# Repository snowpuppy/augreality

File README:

Aug Reality Cornell Cup Project ==
==================================

INTRODUCTION =
==============
This project aims to build an augmented reality simulator device
using a headset and the Intel DE2-i150 development board for the Cornell Cup
Competition. The headset is a custom design which has 3d graphics,
head tracking, gps positioning, and a wide field of view.
This is phase2 of the project. Documentation for phase1 and phase2 can be found
in our doc/ folder. The headset src/ folder is subdivided into all of the software
modules for this project.

DIRECTORY STRUCTURE =
=====================

## headset
##########

$$ headset/src
    This directory contains all source code for the Headset.

$$ headset/test
    This directory contains all test code for the headset (usually proof of concept or simulation code.)

$$ headset/doc
    This directory contains specific documentation related to the headset.

## doc
######
  This directory contains all general documenation for the top level design.

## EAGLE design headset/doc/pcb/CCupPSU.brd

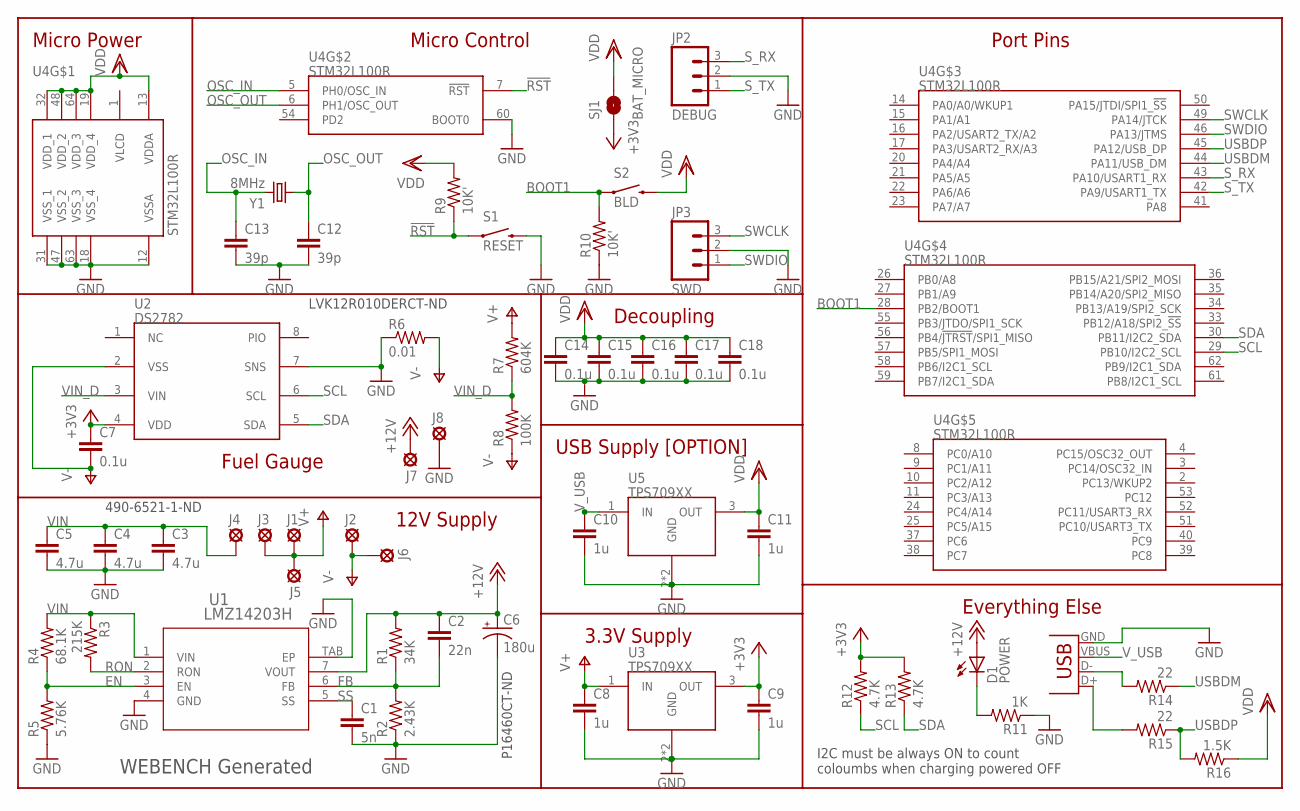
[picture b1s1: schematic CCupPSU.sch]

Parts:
C1: 5n; 1206
C2: 22n; 1206
C3, C4, C5: 4.7u; 1206
C6: 180u; PANASONIC_E
C7, C14, C15, C16, C17, C18: 0.1u; 1206
C8, C9, C10, C11: 1u; 1206
C12, C13: 39p; 1206
D1: POWER; LED-1206
J1, J2, J3, J4, J5, J6, J7, J8: SE14
JP1: USBSMD; USB-MINIB
JP2: DEBUG; 1X03
JP3: SWD; 1X03
R1: 34K; 1206
R2: 2.43K; 1206
R3: 215K; 1206
R4: 68.1K; 1206
R5: 5.76K; 1206
R6: 0.01; 1206
R7: 604K; 1206
R8: 100K; 1206
R9, R10: 10K'; 1206
R11: 1K; 1206
R12, R13: 4.7K; 1206
R14, R15: 22; 1206
R16: 1.5K; 1206
S1: RESET; TACTILE-PTH
S2: BLD; TACTILE-PTH
SJ1: BAT_MICRO; SJ_2S-TRACE
U1: LMZ14203H; TZA07A
U2: DS2782; TSSOP8
U3, U5: TPS709XX; SOT223
U4: STM32L100R; TQFP64
Y1: 8MHz; HC49US

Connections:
!RST!: R9.1, S1.1, U4.7 (!RST!)
+3V3: C7.1, C9.1, R12.2, R13.2, SJ1.1, U2.4 (VDD), U3.3 (OUT)
+12V: C2.1, C6.+, D1.A, J7.MP, R1.2, U1.7 (VOUT)
BOOT1: R10.2, S2.1, U4.28 (PB2/BOOT1)
EN: R4.1, R5.2, U1.3 (EN)
FB: C2.2, R1.1, R2.2, U1.6 (FB)
GND: C1.2, C3.2, C4.2, C5.2, C6.-, C8.2, C9.2, C10.2, C11.2, C12.2, C13.2, C14.2, C15.2, C16.2, C17.2, C18.2, J8.MP, JP1.GND, JP2.2, JP3.2, R2.1, R5.1, R6.1, R10.1, R11.1, S1.3 (2), U1.4 (GND), U1.TAB (EP), U2.7 (SNS), U3.2 (GND), U3.4 (GND), U4.12 (VSSA), U4.18 (VSS_4), U4.31 (VSS_1), U4.47 (VSS_2), U4.60 (BOOT0), U4.63 (VSS_3), U5.2 (GND), U5.4 (GND)
OSC_IN: C13.1, U4.5 (PH0/OSC_IN), Y1.2
OSC_OUT: C12.1, U4.6 (PH1/OSC_OUT), Y1.1
PLED: D1.C, R11.2
RON: R3.2, U1.2 (RON)
SCL: R12.1, U2.6 (SCL), U4.29 (PB10/I2C2_SCL)
SDA: R13.1, U2.5 (SDA), U4.30 (PB11/I2C2_SDA)
SS: C1.1, U1.5 (SS)
SWCLK: JP3.3, U4.49 (PA14/JTCK)
SWDIO: JP3.1, U4.46 (PA13/JTMS)
S_RX: JP2.3, U4.43 (PA10/USART1_RX)
S_TX: JP2.1, U4.42 (PA9/USART1_TX)
USBDM: R14.1, U4.44 (PA11/USB_DM)
USBDP: R15.1, R16.2, U4.45 (PA12/USB_DP)
USB_D+: JP1.D+, R15.2
USB_D-: JP1.D-, R14.2
V+: C8.1, J1.MP, J3.MP, J5.MP, R7.2, U3.1 (IN)
V-: C7.2, J2.MP, J6.MP, R6.2, R8.1, U2.2 (VSS)
VDD: C11.1, C14.1, C15.1, C16.1, C17.1, C18.1, R9.2, R16.1, S2.3 (2), SJ1.2, U4.13 (VDDA), U4.19 (VDD_4), U4.32 (VDD_1), U4.48 (VDD_2), U4.64 (VDD_3), U5.3 (OUT)
VIN: C3.1, C4.1, C5.1, J4.MP, R3.1, R4.2, U1.1 (VIN)
VIN_D: R7.1, R8.2, U2.3 (VIN)
V_USB: C10.1, JP1.VBUS, U5.1 (IN)

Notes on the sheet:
490-6521-1-ND
P16460CT-ND
12V Supply
WEBENCH Generated
LVK12R010DERCT-ND
3.3V Supply
Fuel Gauge
USB Supply [OPTION]
Micro Power
Micro Control
Decoupling
Port Pins
I2C must be always ON to count coloumbs when charging powered OFF
Everything Else

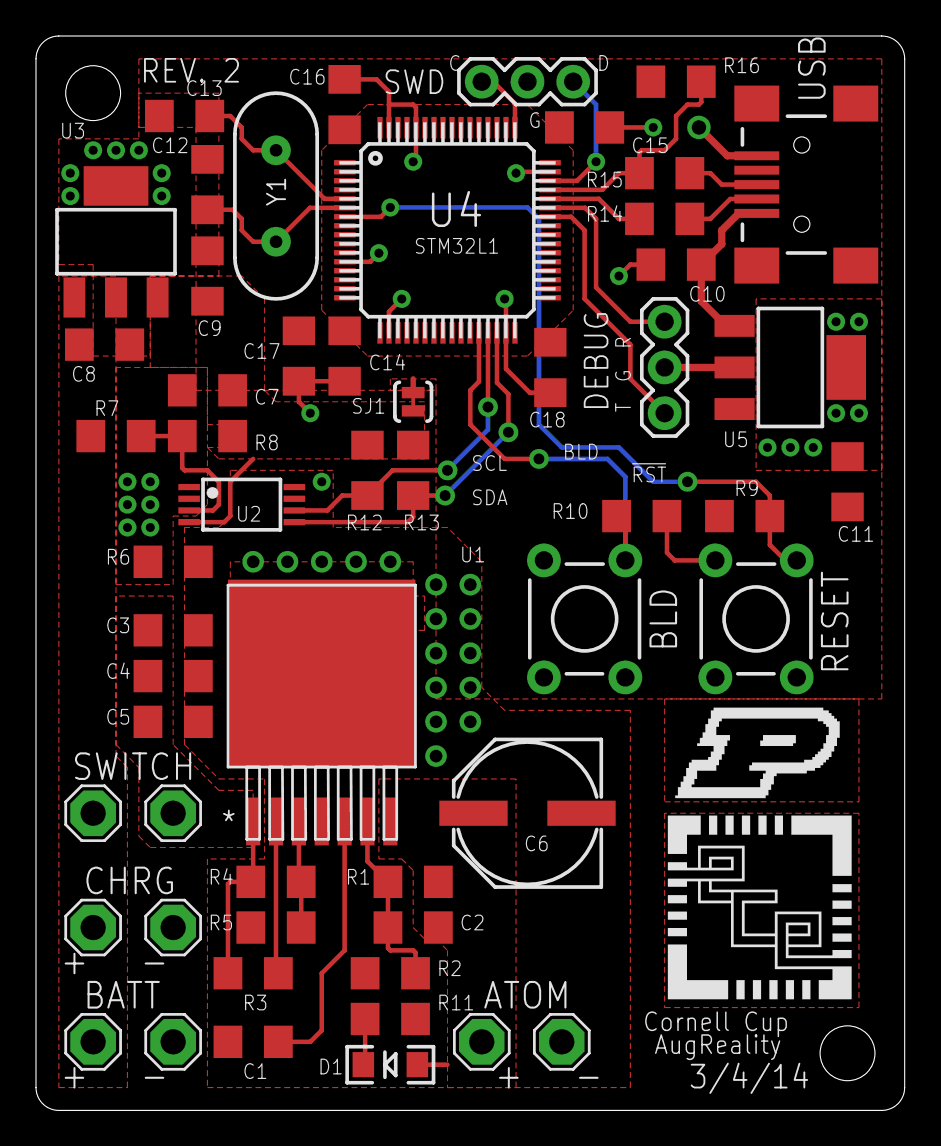
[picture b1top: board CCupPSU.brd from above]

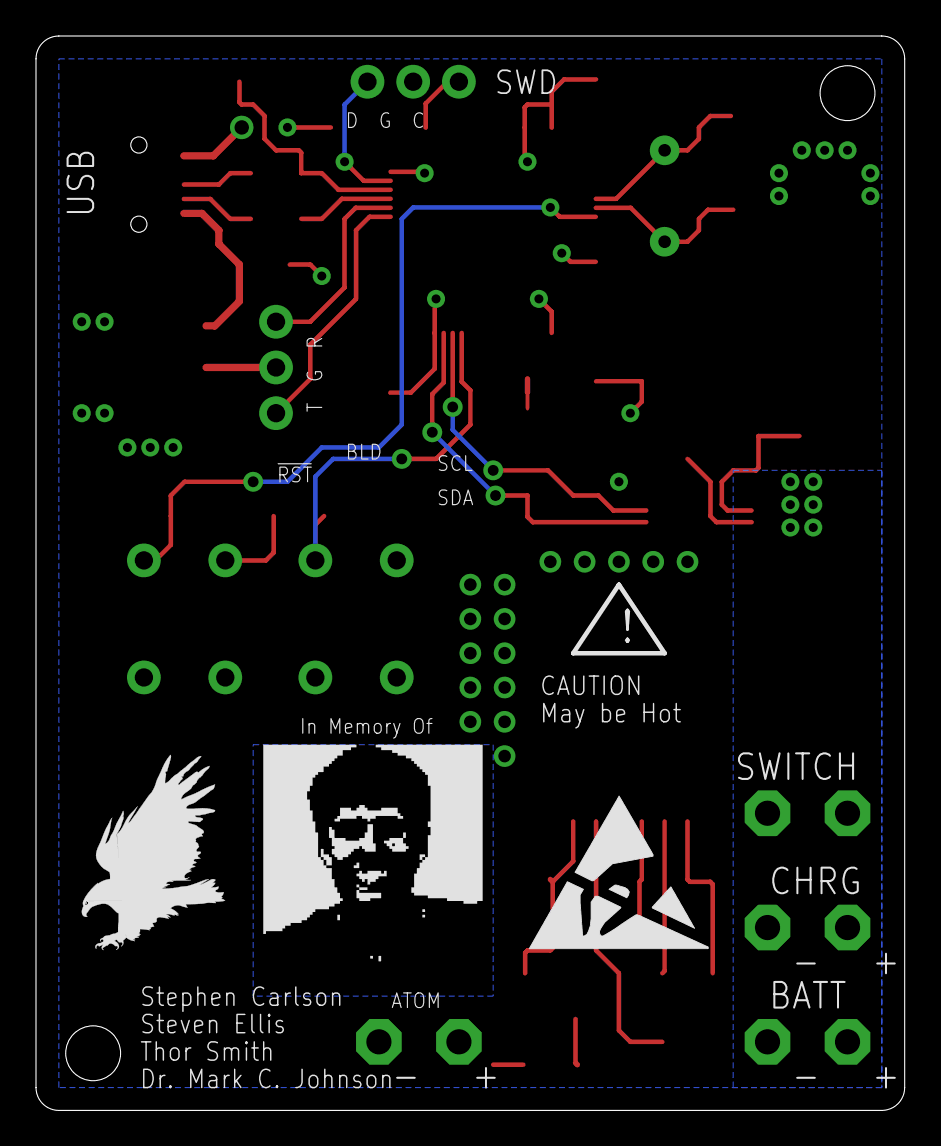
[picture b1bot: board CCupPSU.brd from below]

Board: 2 copper layers, 48.3 x 59.7 mm, 57 parts (2 on the bottom side), 28 nets.

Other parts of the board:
U$1: ESD_10.00
U$2: EAGLE-PLC-8MM

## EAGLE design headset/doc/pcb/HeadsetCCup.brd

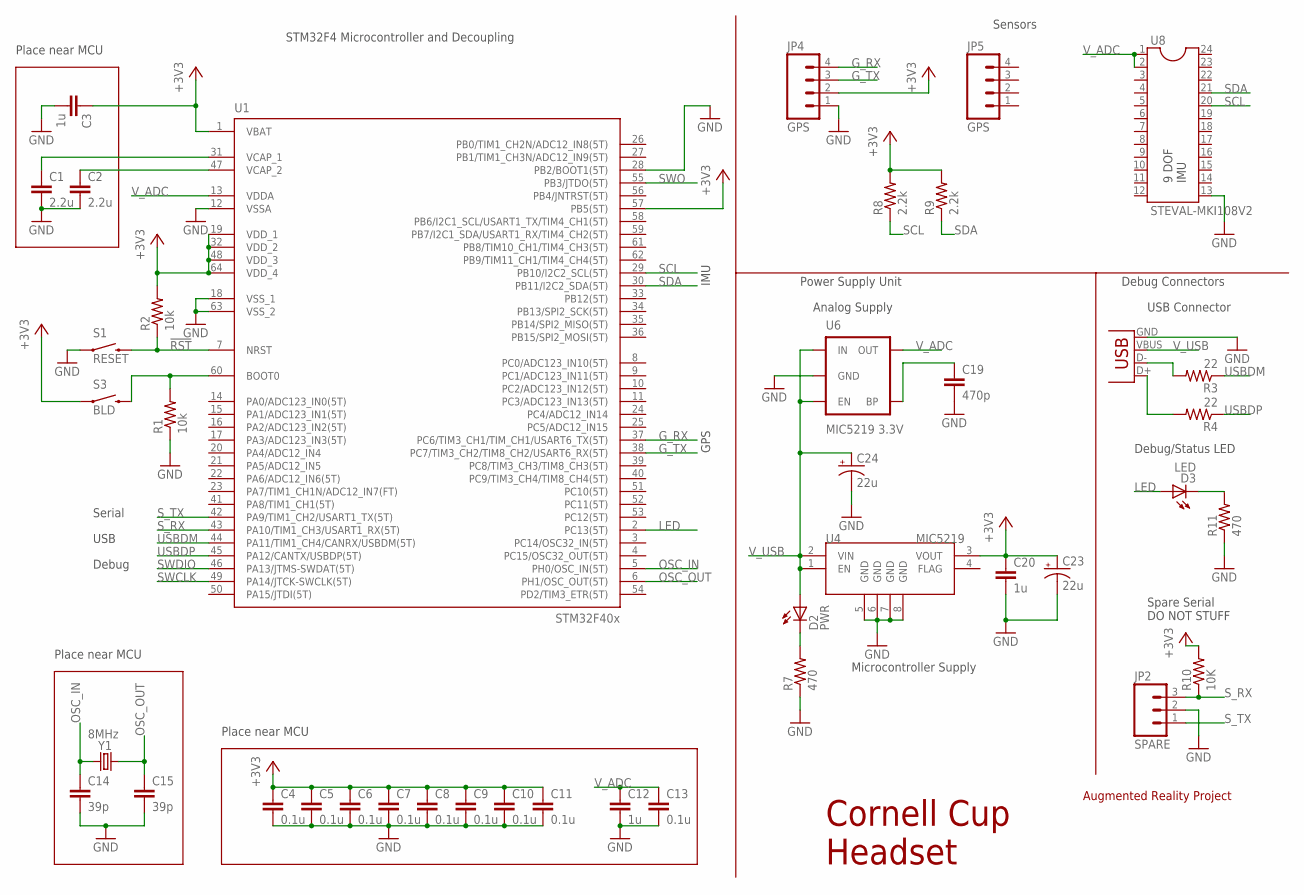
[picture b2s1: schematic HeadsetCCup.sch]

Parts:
C1, C2: 2.2u; 1206
C3, C12, C20: 1u; 1206
C4, C5, C6, C7, C8, C9, C10, C11, C13: 0.1u; 1206
C14, C15: 39p; 1206
C19: 470p; 1206
C23, C24: 22u; PANASONIC_D
D2: PWR; LED-1206
D3: LED; LED-1206
JP1: USBSMD; USB-MINIB
JP2: SPARE; 1X03
JP4, JP5: GPS; 1X04
R1, R2: 10k; 1206
R3, R4: 22; 1206
R7, R11: 470; 1206
R8, R9: 2.2k; 1206
R10: 10K; 1206
S1: RESET; TACTILE-PTH
S3: BLD; TACTILE-PTH
U1: STM32F405RGT6; TQFP64
U4: MIC5219; MSOP8
U6: MIC5219 3.3V; SOT23-5
U8: STEVAL-MKI108V2; DIL24-6
Y1: 8MHz; HC49US

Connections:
!RST!: R2.1, S1.3 (2), U1.7 (NRST)
+3V3: C3.1, C4.1, C5.1, C6.1, C7.1, C8.1, C9.1, C10.1, C11.1, C20.1, C23.+, JP4.2, R2.2, R8.2, R9.2, R10.2, S3.1, U1.1 (VBAT), U1.19 (VDD_1), U1.32 (VDD_2), U1.48 (VDD_3), U1.57 (PB5(5T)), U1.64 (VDD_4), U4.3 (VOUT)
BOOT0: R1.2, S3.3 (2), U1.60 (BOOT0)
GND: C1.2, C2.2, C3.2, C4.2, C5.2, C6.2, C7.2, C8.2, C9.2, C10.2, C11.2, C12.2, C13.2, C14.2, C15.2, C19.2, C20.2, C23.-, C24.-, JP1.GND, JP2.2, JP4.1, R1.1, R7.1, R11.1, S1.1, U1.12 (VSSA), U1.18 (VSS_1), U1.28 (PB2/BOOT1(5T)), U1.63 (VSS_2), U4.5 (GND), U4.6 (GND), U4.7 (GND), U4.8 (GND), U6.2 (GND), U8.13
G_RX: JP4.4, U1.37 (PC6/TIM3_CH1/TIM_CH1/USART6_TX(5T))
G_TX: JP4.3, U1.38 (PC7/TIM3_CH2/TIM8_CH2/USART6_RX(5T))
LED: D3.A, U1.2 (PC13(5T))
LED_LED: D3.C, R11.2
OSC_IN: C14.1, U1.5 (PH0/OSC_IN(5T)), Y1.1
OSC_OUT: C15.1, U1.6 (PH1/OSC_OUT(5T)), Y1.2
PWR_LED: D2.C, R7.2
SCL: R8.1, U1.29 (PB10/I2C2_SCL(5T)), U8.20
SDA: R9.1, U1.30 (PB11/I2C2_SDA(5T)), U8.21
SWCLK: U1.49 (PA14/JTCK-SWCLK(5T))
SWDIO: U1.46 (PA13/JTMS-SWDAT(5T))
SWO: U1.55 (PB3/JTDO(5T))
S_RX: JP2.3, R10.1, U1.43 (PA10/TIM1_CH3/USART1_RX(5T))
S_TX: JP2.1, U1.42 (PA9/TIM1_CH2/USART1_TX(5T))
USBDM: R3.1, U1.44 (PA11/TIM1_CH4/CANRX/USBDM(5T))
USBDP: R4.1, U1.45 (PA12/CANTX/USBDP(5T))
USB_D+: JP1.D+, R4.2
USB_D-: JP1.D-, R3.2
VCAP1: C1.1, U1.31 (VCAP_1)
VCAP2: C2.1, U1.47 (VCAP_2)
V_ADC: C12.1, C13.1, U1.13 (VDDA), U6.5 (OUT), U8.1, U8.2
V_BYP: C19.1, U6.4 (BP)
V_USB: C24.+, D2.A, JP1.VBUS, U4.1 (EN), U4.2 (VIN), U6.1 (IN), U6.3 (EN)

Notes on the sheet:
Place near MCU
STM32F4 Microcontroller and Decoupling
Debug Connectors
Microcontroller Supply
Analog Supply
Power Supply Unit
Sensors
Augmented Reality Project
Cornell Cup Headset
IMU
GPS
Serial
9 DOF IMU
Spare Serial DO NOT STUFF
USB Connector
Debug/Status LED
USB
Debug

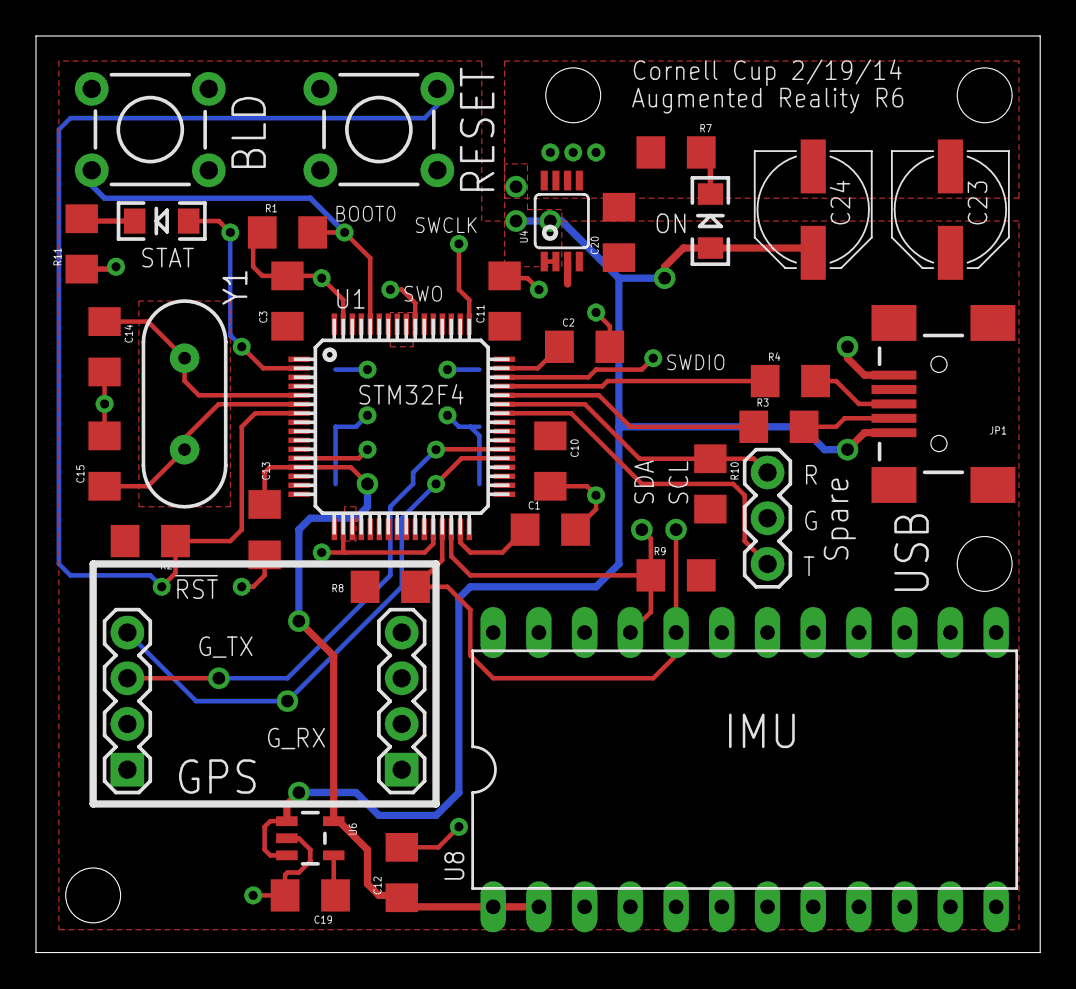
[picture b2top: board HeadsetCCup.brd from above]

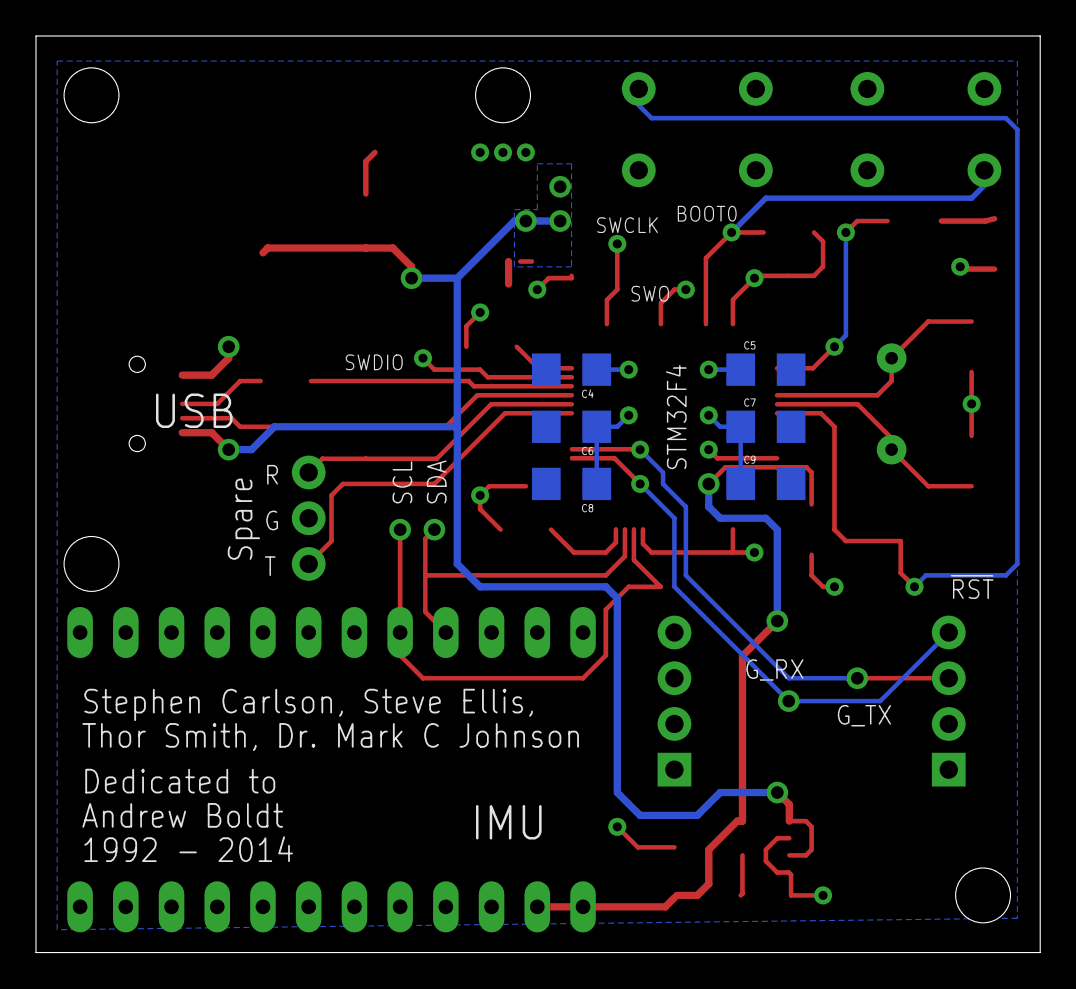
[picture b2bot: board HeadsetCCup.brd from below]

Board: 2 copper layers, 55.8 x 50.9 mm, 41 parts (6 on the bottom side), 24 nets.

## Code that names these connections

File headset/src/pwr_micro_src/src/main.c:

/*
 * Cornell Cup 2014 - Augmented Reality Simulator
 *
 * Stephen Carlson
 * Steven Ellis
 * Thor Smith
 * Dr. Mark C. Johnson
 *
 * main.c - Power supply microcontroller source code
 */

#include "main.h"

// Flag bits for the flags byte
#define FLAG_REPORT 0x01U
#define FLAG_ALARM 0x02U
#define FLAG_STOP 0x04U

// Flags byte used to handle reporting over USB
static volatile uint16_t flags;

/**
 * GPIO initialization
 *
 * Turn on the GPIO, set the unused pins to input pull down, then kill clocks on unused
 * modules
 */
static void initGPIO(void) {
	GPIO_InitTypeDef gpio;
	// Turn all GPIO on
	RCC->AHBENR |= RCC_AHBENR_GPIOAEN | RCC_AHBENR_GPIOBEN | RCC_AHBENR_GPIOCEN |
		RCC_AHBENR_GPIODEN;
	__DSB();
	// PA11, PA12 are USB; PA13, PA14, PA15 are JTAG (PA9 and PA10 are the serial port)
	gpio.GPIO_Mode = GPIO_Mode_IN;
	gpio.GPIO_PuPd = GPIO_PuPd_DOWN;
	gpio.GPIO_Speed = GPIO_Speed_400KHz;
	gpio.GPIO_OType = GPIO_OType_OD;
	gpio.GPIO_Pin = (uint16_t)0x07FFU;
	GPIO_Init(GPIOA, &gpio);
	// PB10, PB11 are I2C; PB2 has external pull down
	gpio.GPIO_Pin = (uint16_t)0xF3FBU;
	GPIO_Init(GPIOB, &gpio);
	// All PC unused
	gpio.GPIO_Pin = (uint16_t)0xFFFFU;
	GPIO_Init(GPIOC, &gpio);
	// PD2 only pin
	gpio.GPIO_Pin = (uint16_t)0xFFFFU;
	GPIO_Init(GPIOD, &gpio);
	// Turn off C and D which are not used
	RCC->AHBENR &= ~(RCC_AHBENR_GPIOCEN | RCC_AHBENR_GPIODEN);
}

/**
 * USB initialization
 *
 * Initializes the USB peripheral and turns on the internal USB pull-up resistor
 */
static void initUSB(void) {
	EXTI_InitTypeDef exti;
	GPIO_InitTypeDef gpio;
	// Power up USB
	RCC->APB1ENR |= RCC_APB1ENR_USBEN;
	__DSB();
	// Set up the pins for USB
	// NOTE The pin mode MUST be input! NOT alternate function!
	gpio.GPIO_Pin = GPIO_Pin_11 | GPIO_Pin_12;
	gpio.GPIO_Mode = GPIO_Mode_IN;
	gpio.GPIO_OType = GPIO_OType_PP;
	gpio.GPIO_PuPd = GPIO_PuPd_UP;
	gpio.GPIO_Speed = GPIO_Speed_40MHz;
	GPIO_Init(GPIOA, &gpio);
	// Set AF modes for USB
	GPIO_PinAFConfig(GPIOA, GPIO_PinSource11, GPIO_AF_USB);
	GPIO_PinAFConfig(GPIOA, GPIO_PinSource12, GPIO_AF_USB);
	// Turn on USB pull-up resistor
	SYSCFG->PMC |= SYSCFG_PMC_USB_PU;
	usbInit();
	// Configure EXTI line 18 to interrupt in rising edge mode
	exti.EXTI_Line = EXTI_Line18;
	exti.EXTI_LineCmd = ENABLE;
	exti.EXTI_Mode = EXTI_Mode_Interrupt;
	exti.EXTI_Trigger = EXTI_Trigger_Rising;
	EXTI_Init(&exti);
	// Clear any pending interrupts
	EXTI->PR &= EXTI_PR_PR18;
	// Enable USB IRQs
	NVIC_SetPriority(USB_LP_IRQn, 2);
	NVIC_EnableIRQ(USB_LP_IRQn);
	NVIC_SetPriority(USB_FS_WKUP_IRQn, 3);
	NVIC_EnableIRQ(USB_FS_WKUP_IRQn);
}

/**
 * System initialization
 *
 * Initializes the interrupt system, enables GPIO clocks, and sets up each peripheral
 */
static void init(void) {
	flags = 0x00U;
	// Priority group #3 configuration
	NVIC_SetPriorityGrouping(3);
	initGPIO();
	// EXTI and SYSCFG clocks on
	RCC->APB2ENR |= RCC_APB2ENR_SYSCFGEN;
	// Set up the peripherals, the debug serial is not used anymore so shut it off for power
	i2cInit();
	rtcInit();
	initUSB();
	// Enable interrupts for all peripherals
	__enable_fault_irq();
	__enable_irq();
}

/**
 * Prepares for STOP low-power mode, arming RTC for 1 minute. Switches the clock to MSI.
 *
 * This should probably be called from USB suspend.
 */
static void enterStopMode(void) {
	switchToMSI();
	flags |= FLAG_STOP;
	rtcSetAlarmFrequency(RTC_1M);
}

/**
 * Prepares for normal run mode, arming RTC for 1 second. Switches the clock to HSE+PLL.
 *
 * This should probably be called from USB resume.
 */
static void exitStopMode(void) {
	switchToHSE();
	flags &= ~FLAG_STOP;
	rtcSetAlarmFrequency(RTC_1S);
}

/**
 * Called by the startup to run the main program
 */
int main(void) {
	// Avoid excess reads of global variable
	uint32_t lFlags;
	// Temporary for I2C transactions
	uint8_t value[2];
	// Initialize the system
	init();
	while (1) {
		// Disable interrupts to safely read and write flags variable
		__disable_irq();
		lFlags = flags;
		if ((lFlags & FLAG_ALARM) != 0)
			// Shut off the alarm clock
			flags = lFlags & ~FLAG_ALARM;
		__enable_irq();
		// Get voltage registers from the fuel gauge every second
		if (lFlags & FLAG_ALARM) {
			if (usbIsConnected() && i2cReadRegister(0x34, 0x0C, value, 2)) {
				// DS2782 datasheet Figure 4: V = 9876543210XXXXX
				uint32_t volts = ((uint32_t)value[0] << 3) | ((uint32_t)value[1] >> 5);
				// 1 lsb = 4.88 mV, 39/8 = 4.875 mV, calculate voltage
				printf("%u\r\n", (unsigned int)((volts * 39) >> 3));
			}
		} else {
			// Go into STOP mode if unplugged, or SLEEP if plugged ni
			if (lFlags & FLAG_STOP)
				STOP();
			else
				SLEEP();
		}
	}
	return 0;
}

/**
 * Called when the USB interface receives a suspend event, indicating that the host has powered
 * down.
 */
void usbPowerDown(void) {
	// Disable reporting over USB
	flags &= ~(FLAG_ALARM | FLAG_REPORT);
	// Enter STOP mode
	enterStopMode();
}

/**
 * Called every 1s to read the fuel gauge.
 */
void IRQ RTC_Alarm_IRQHandler(void) {
	// Shut off the alarm clock
	RTC->ISR &= ~RTC_ISR_ALRAF;
	EXTI->PR &= EXTI_PR_PR17;
	// Read flags
	const uint32_t lFlags = flags;
	if (lFlags & FLAG_REPORT)
		// Assert ALARM signal if needed
		flags = lFlags | FLAG_ALARM;
}

/**
 * Called on USB wake-up detected.
 */
void IRQ USB_FS_WKUP_IRQHandler(void) {
	// Shut off the alarm clock
	EXTI->PR &= EXTI_PR_PR18;
	// Exit STOP mode, as the host has connected and powered up
	exitStopMode();
	// Reset the USB peripheral to prepare for re-enumeration
	SYSCFG->PMC |= SYSCFG_PMC_USB_PU;
	usbInit();
	// Enable reporting over USB
	flags = (flags & ~FLAG_ALARM) | FLAG_REPORT;
}

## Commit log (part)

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2013-05-23 Updated readme, added src and doc folders, added AUTHORS file.
2013-06-23 changed directory structure to have a headset and ccu module directories. Each module has its own src, test, and doc directories.
2013-06-29 Add the STM32 source which successfully boots the STM32F4Discovery board.
2013-09-09 Add headset schematic revision #1, EAGLE libraries, and project library
2013-09-11 Update design constraint analysis version 2, incorporate team member and staff feedback
2013-09-13 Add homework 3 to documentation
2013-09-21 Add I2C and UART example, successfully decodes all 9 axes and reports some of them back over USART3 (can be changed by modifying the printf)
    Port connections:
    I2C SCL -> PB6
    I2C SDA -> PB9
    USART3 TX <- PB10
2013-09-23 Ignore stlink.mk
2013-09-27 Update headset schematic revision 2 (again), almost ready for route
2013-09-29 added V3 and V4 classes
2013-10-02 Add TCSP 05 PCB/Layout Narrative
2013-10-05 Added python script to calculate dX and dY values for GPS to get an idea of how accurate decimal places are. The constants used were pulled from Wikipedia. A link will be posted on the wiki.
2013-10-08 Update headset PCB and schematic to hopefully the last version
2013-10-11 added design review.
2013-10-12 Update block diagram in design review to fix text background problem
2013-10-17 Added mounting hole to PCB
2013-10-22 Substantially cleaned up I2CExample, should work the same but is not tested
2013-10-23 Add battery fuel gauge monitoring driver, working to get voltage and SOC%, accuracy of SOC% needs to be tested
2013-10-28 added draft of gui for ccu.
2013-10-29 SPI Slave code working well, clean up code in a few other projects and add extended fuel gauge graph
2013-10-30 Added TCSP 8, patent liability.
2013-11-01 Adjust STM32 booter to boot and heartbeat the ACTUAL PCB!
2013-11-01 Add all-peripherals test code which exercises fuel gauge, XBee, Raspberry PI, GPS, and external serial. Add GPS test data taken from a campus run using the production hardware and GPS configuration u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
2013-11-06 added current network changes. Also added software design homework.
2013-11-06 Add IMU/I2C test exercise code to all peripherals test example (yes, it works)
2013-11-06 added Reliability and safety presenation.
2013-11-09 copied USBToSerial/ from the test folder to the micro_src folder for final development.
2013-11-13 added spi functionality to send data from xbee to gpu. Not finished yet.
2013-11-13 added safety and reliability analysis.
2013-11-14 adapted for gps.
2013-11-14 updated packets.h, no longer depends on user defined int types.
2013-11-16 added specification for packe types between headset and ccu.
2013-11-16 added fuel guage and rssi values to buffer that is streamed through spi to gpu.
2013-11-17 disabled fuel guage data.
2013-11-17 presentation for tscp 3 added
2013-11-17 gameobject class added
2013-11-17 Added low pass filter for IMU data.
2013-11-19 fix data size in comm and led setup.
2013-11-21 added new 3D models
2013-11-22 modified spi buffer receive routine to support flusing the spi buffer on command.
2013-11-22 Attempted fix of USB to Serial drivers, but no go. Something is different between the test project and the actual headset project.
2013-11-25 fixed gui to match dimensions of final screen.
2013-11-25 Added initial filtering with the gyro, noise drastically reduced without transient response or drift problems, but need to properly rotate gyro into the world frame of reference
2013-11-26 added python script to test sending a file through xbee.
2013-11-27 added makefile for ccu.
2013-11-27 working to support file transfer for headset
2013-11-27 Merged spiReceivedByte function back in. Changed Makefile for headset to auto-generate the packets.h and packets.c file and add them to the directory. These auto-generated files were also added to th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
2013-11-27 test file capture adapted for updated packet info.
2013-11-28 updated python file capture to stop when entire file received.
2013-12-02 pythonSerialTest now emulates sending a file packet and packetLib.c was updated.
2013-12-03 Successfully ran test for python to c network communication.
2013-12-03 The packet daemon has been updated to include a thread for servicing requests from the gui/simulation.
2013-12-03 Alec changed IMU filter in main.c to simple low-pass filter
2013-12-03 fixed xbee read init
2013-12-03 Alec made modifications in attempt to fix rotation issues found after filtering.
2013-12-03 updated library to support 16 byte address...
2013-12-04 seperated python tests.
2013-12-04 Added python first python test functions to help debugging wireless traffic.
2013-12-04 pacman level
2013-12-05 Several fixes to file transfer
2013-12-05 Finished creating the api to test packets in python. It is now possible to connect the gui to the library that communicates with the headset. The next step is to finish packet processing on the heads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
2013-12-06 added a test for receiving update packets.
2013-12-06 updated spi test which contains all info to be receive over spi.
2013-12-06 modified tests to work with relative directories.
2013-12-06 added exit condition for test script.
2013-12-08 Added product manual word doc
2013-12-09 added GPL license and readme for the pi code
2013-12-09 modifications to integrate file transfer with rendering
2013-12-09 newlines edited
2013-12-09 previous commit now runs
2013-12-09 updated run script
2013-12-09 Updated Alec's description.
2013-12-09 Finished references. Ready for submission.
2013-12-11 added pellet texture
2013-12-24 Add a copy of the wiki update script, and update uniflash to work with dfu-util 0.6+
2014-02-06 Align headset data to word boundary to possibly fix mis aligned store issue
2014-02-08 Added Cornell Cup Application.
2014-02-11 updated performance metrics section of midreview ppt
2014-02-11 removed so could merge with main branch.
2014-02-12 Added first PCB draft for Cornell Cup headset.
2014-02-13 Timeline slides updated to be readable. Budget slides updated to fill in missing info and to remove old info. Steven's modifications to performance metrics added back in.
2014-02-14 Update presentation with some of the changes from Dr. J and GH.
2014-02-15 Revise most of GH and Dr. J changes
    Need:
    - picture replacements
    - timeline with larger font
    - budget audit
2014-02-16 ppt update
2014-02-17 Added timeline file.
2014-02-19 Updated accept api to send gps origin information to the headset. An application has been added for the ccu testing code that sends querys for the headset's gps and imu data and then displays it.
2014-03-05 updated software diagram
2014-03-11 new rendering stuff
2014-03-11 camera movement now uses standard WASD controls
2014-03-18 Add skeleton for Cornell Cup microcontroller codes; all references to the fuel gauge and XBee have been removed. Untested.
2014-03-18 removed ccup code from phase1.
2014-03-18 Wrote sensor transmit code and tested sensor data collection over Serial
2014-03-18 Sensor data processing will be combined with networking. Both will be run in the same process in seperate threads.
2014-03-18 removed old ccu from phase2 project.
2014-03-19 Added thread for collecting gps/imu data. Modified sensor micro src so that it does not find an origin. This is easier because it makes serial traffic one-way. It was also discovered that the serial 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
2014-03-23 Add include files and start up scripts for power microcontroller
2014-03-25 Updated timeline and added another milestone.
2014-03-30 extra copies of gputhreadpyinterface for test application
2014-03-30 Started updating python files to use the new api for collecting sensor information. It is my goal to support both python simulations as well as c++ simulations. The goal of supporting python is that 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
2014-03-30 Added an interface for communication of a python program to the gpu rendering code.
2014-03-31 Wrote interface between gpu software and sensor data. The interface has not been compiled or tested yet. That is the next step.
2014-03-31 added missing files for rendering code
2014-04-01 fixed data collection thread and added a little filtering on possible values.
2014-04-02 Power micro code compiles, but does not want to upload
2014-04-05 Fixed numerous issues. USB on STM32L1 Works!!!
    Note that the ST LINK GUI does not reload binaries in the Program dialog! Fixed the common.mk to point to CLI flash utility to allow "make upload"
2014-04-05 Attempt #2 at fixing USB, for real this time
2014-04-05 updated serial test for sensor data.
2014-04-06 fixed again. First time done incorrectly.
2014-04-08 re-structured networking code for final implemenation.
2014-04-10 Power microcontroller has working rtc drivers. Mass header clean up.
2014-04-12 some more content in assembly appendix, and the materials table has been added
2014-04-13 updated update objs code.
2014-04-13 Changed objinfo structure to add the ability to set an objects 3rd dimensional coordinate. I also fixed the switch statement for sending out packets periodically.
2014-04-16 Experimintal test application.
2014-04-16 Added logic to hide pellets. Not tested.
2014-04-17 Update report, and add several changes to power microcontroller code.
2014-04-18 Update final report, add pictures to test section, need captions
2014-04-19 added math library to gpsIMUThread.
2014-04-19 final report update
2014-04-20 Update report and status
2014-04-21 Moved final report to a seperate folder containing all documents for the final submission.
2014-04-21 Finish testing section and schematic/theory of operation/PCB section. Reformat to match CCup guideline of calibri 11 pt.
2014-04-21 Update report status, formatting fix
2014-04-21 Add schematic and PCB layout appendices.
2014-04-21 added survey appendix
2014-04-21 survey response appendix and writeup updated
2014-04-22 Updated Recommendations and Next steps, Project Execution, and Failure Analysis.
2014-04-22 Fix some formatting, add conclusions to Failure Mode Analysis, add a line regarding Pi matching to Tech Specs Phase2
2014-04-23 User interface is complete except that it needs to call underlying functions to make traversing it significant. All underlying functions have been defined, but not fully implemented.
2014-04-24 Power microcontroller successfully enters Zeropower (or close to) state, thanks to turning on pull-up and pull-down resistors.
    Still does not resume USB correctly on wake up.
2014-04-26 fixes to application.
2014-04-26 Updated the gui interface to make the interface consistent with the current implementation.
2014-04-26 Essentially one-timed the fuel gauge reading, works in parallel with gps
2014-04-26 fixed getAccept.
2014-04-26 made return values signed
2014-04-26 Added ability to accept/deny in gui.
2014-04-26 fixed reset origin.
2014-04-26 collision fix
2014-04-26 fixed getReceivedFile in gui interface.
2014-04-26 ghost paths all inside maze
2014-04-26 working to make launch start simulation.
2014-04-27 maybe fixed file sending and added the rest of the updateObj code.
2014-04-27 more fixes for sendFile.
2014-04-27 ../networking_src/packetLib.cpp
2014-04-27 added imu/gps/battery stuff back in.
2014-04-28 removed debug from gpsIMU thread.
2014-04-28 fixed minor error gui.
2014-04-28 Add final presentation.
2014-04-28 Include Dr. J's suggestions in final presentation draft
2014-04-29 Update presentation to add software diagram
2014-04-30 added wireless update functionality.
2014-05-01 fixed cliet application so it will exit if render code exits.
2014-05-01 networking status goes to disconnected upon losing signal.
2014-05-01 added way to launch client manually...
2014-05-01 Changed the origin in the pacman simulation.
2014-05-02 Hard-iron correction for magnetometer implemented
2014-06-06 Finished modifications to make the configuration file changes correct and seamless with both the rendering software and the simulation software. There were problems in the configuration reading softw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
2014-06-09 modified gui to dynamically find and launch simulations.
2014-06-10 Added an API call for translating GPS coordinates into x,y coordinates. This will make it easier/possible to write an application driven by GPS based coordinates. Simply translate your GPS coordinate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

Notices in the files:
parts and their libraries:
SparkFun-Passives: Licensing: CC v3.0 Share-Alike You are welcome to use this library for commercial purposes.
